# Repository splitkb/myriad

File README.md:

# Myriad

This repository stores the public documentation for the [Myriad System](https://myriad.splitkb.com/). Did you see any mistakes? Feel free to submit a pull request!

## Symbols & footprints
You can find KiCad symbols and footprints [here](assets/kicad/).

## Example projects
You can find some example projects [here](assets/example_projects/).

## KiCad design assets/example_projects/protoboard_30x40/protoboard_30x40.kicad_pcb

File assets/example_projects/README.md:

# Myriad Example projects
Having trouble getting started with your Myriad project? Why not [take a look](https://github.com/splitkb/myriad/archive/refs/heads/main.zip) at these example projects to get an idea of what the end result should look like.

_(Having trouble finding this directory in the ZIP? It's under `assets/kicad`!)_

## protoboard_??x??

Simple prototyping board. Exposes basic GPIO functionality on the bottom two rows, while providing 3-long strips on the rest of the card. You can use this to build your own simple modules, without having to get a PCB manufactured.

## breakout_22x30

Breakout board. Exposes all currently-available Myriad pins, making it ideal if you want to try connecting external hardware to it.

## Licensing

These files are available for **non-commercial use only**. See [https://myriad.splitkb.com/specification/terms_of_use.html](https://myriad.splitkb.com/specification/terms_of_use.html) for more information.

## More information

Are you looking for the specification, or just want to know more about the Myriad system in general? Visit [https://myriad.splitkb.com/](https://myriad.splitkb.com/)!

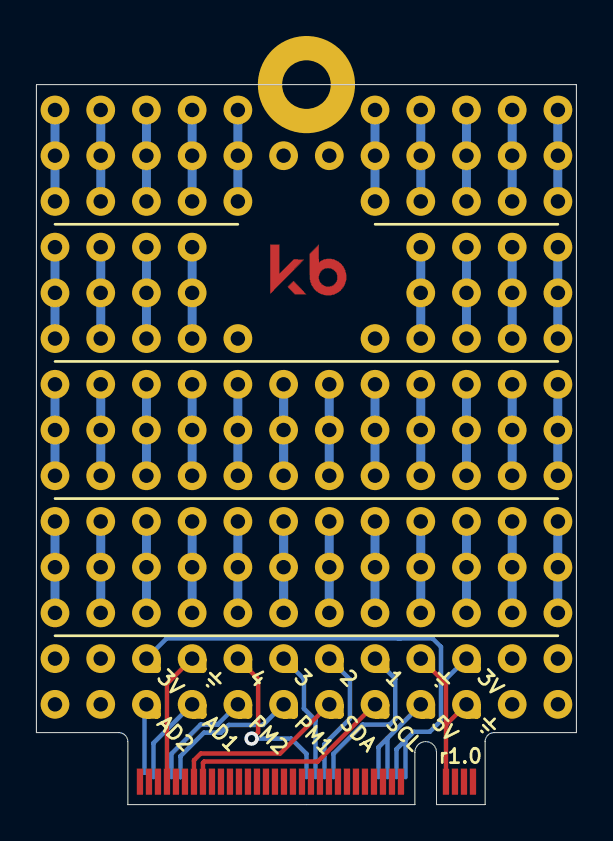
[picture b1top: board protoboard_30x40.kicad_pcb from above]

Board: 2 copper layers, 30.0 x 40.0 mm, 17 parts (0 on the bottom side), 11 nets.

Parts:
J1: Myriad_Module_Connector; Myriad_Module_30x40mm
J2: AD1; ProtoPad
J3: AD2; ProtoPad
J4: PM1; ProtoPad
J5: PM2; ProtoPad
J6: 1; ProtoPad
J7: 2; ProtoPad
J8: 3; ProtoPad
J9: 4; ProtoPad
J10: SDA; ProtoPad
J11: SCL; ProtoPad
J12: 5V; ProtoPad
J13, J16: 3V; ProtoPad
J14, J15, J17: GND; ProtoPad

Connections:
+3V3: J1.16 (PWR_3V), J1.18 (PWR_3V), J13.1, J16.1
+5V: J1.20 (PWR_5V), J1.22 (PWR_5V), J12.1
GND: J1.1 (GND), J1.7 (GND), J1.40 (GND), J1.46 (GND), J1.54 (GND), J1.57 (GND), J1.64 (GND), J1.69 (GND), J1.70 (GND), J14.1, J15.1, J17.1
unnamed: J1.17 (PWR_RAW), J1.19 (PWR_RAW), J1.21 (PWR_RAW), J1.23 (PWR_RAW)
unnamed: J1.32 (GPIO_1), J6.1
unnamed: J1.34 (GPIO_2), J7.1
unnamed: J1.36 (GPIO_3), J8.1
unnamed: J1.38 (GPIO_4), J9.1
unnamed: J1.61 (I2C_SCL), J11.1
unnamed: J1.63 (I2C_SDA), J10.1
unnamed: J1.68 (PWM_2), J5.1

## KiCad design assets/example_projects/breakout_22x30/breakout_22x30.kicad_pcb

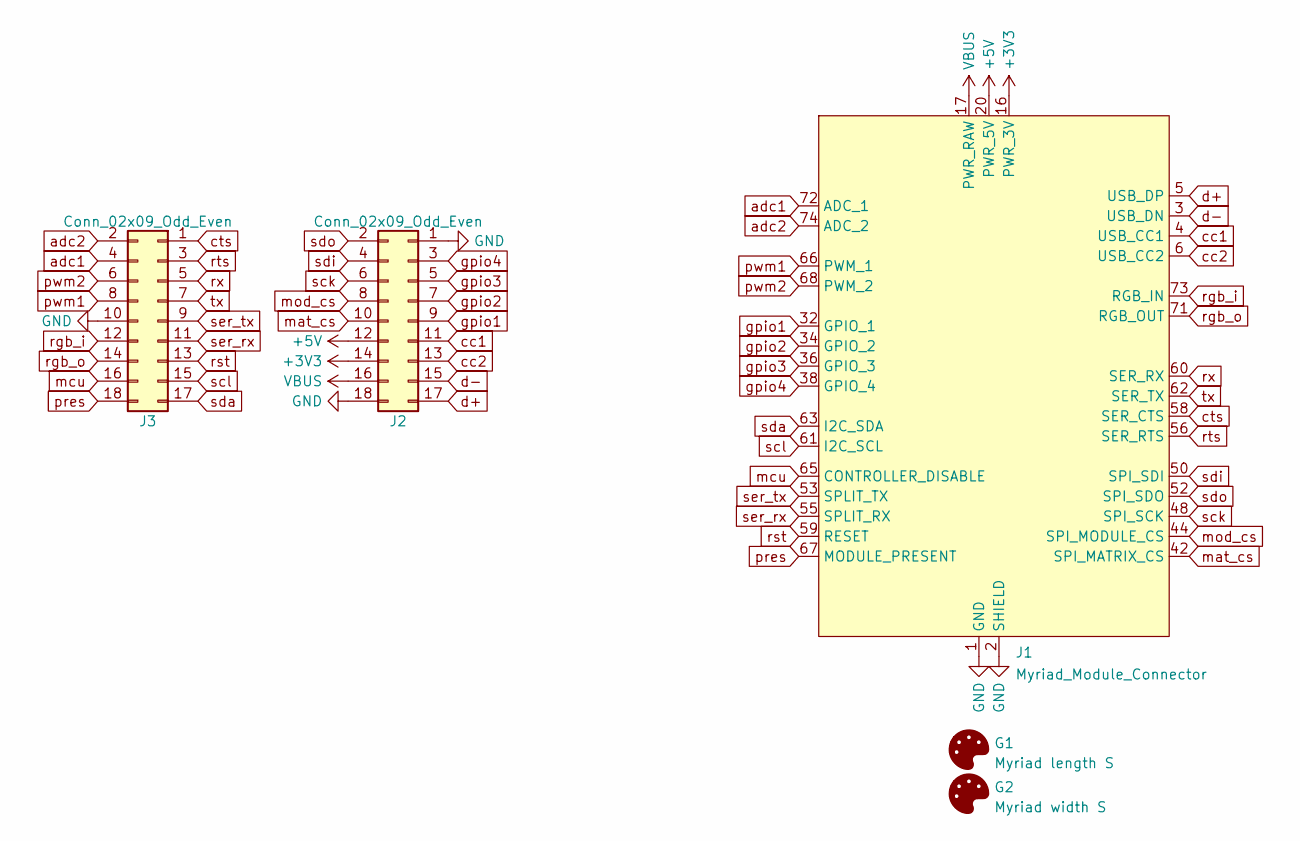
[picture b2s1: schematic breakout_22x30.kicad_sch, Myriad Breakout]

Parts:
G1: Myriad length S; Myriad_length-s
G2: Myriad width S; Myriad_width-s
J1: Myriad_Module_Connector; Myriad_Module_22x30mm
J2, J3: Conn_02x09_Odd_Even; PinSocket_2x09_P2.54mm_Vertical

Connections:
+3V3: J1.16 (PWR_3V), J1.18 (PWR_3V), J2.14
+5V: J1.20 (PWR_5V), J1.22 (PWR_5V), J2.12
GND: J1.1 (GND), J1.2 (SHIELD), J1.7 (GND), J1.40 (GND), J1.46 (GND), J1.54 (GND), J1.57 (GND), J1.64 (GND), J1.69 (GND), J1.70 (GND), J2.1, J2.18, J3.10
VBUS: J1.17 (PWR_RAW), J1.19 (PWR_RAW), J1.21 (PWR_RAW), J1.23 (PWR_RAW), J2.16
adc1: J1.72 (ADC_1), J3.4
adc2: J1.74 (ADC_2), J3.2
cc1: J1.4 (USB_CC1), J2.11
cc2: J1.6 (USB_CC2), J2.13
cts: J1.58 (SER_CTS), J3.1
d+: J1.5 (USB_DP), J2.17
d-: J1.3 (USB_DN), J2.15
gpio1: J1.32 (GPIO_1), J2.9
gpio2: J1.34 (GPIO_2), J2.7
gpio3: J1.36 (GPIO_3), J2.5
gpio4: J1.38 (GPIO_4), J2.3
mat_cs: J1.42 (SPI_MATRIX_CS), J2.10
mcu: J1.65 (CONTROLLER_DISABLE), J3.16
mod_cs: J1.44 (SPI_MODULE_CS), J2.8
pres: J1.67 (MODULE_PRESENT), J3.18
pwm1: J1.66 (PWM_1), J3.8
pwm2: J1.68 (PWM_2), J3.6
rgb_i: J1.73 (RGB_IN), J3.12
rgb_o: J1.71 (RGB_OUT), J3.14
rst: J1.59 (RESET), J3.13
rts: J1.56 (SER_RTS), J3.3
rx: J1.60 (SER_RX), J3.5
sck: J1.48 (SPI_SCK), J2.6
scl: J1.61 (I2C_SCL), J3.15
sda: J1.63 (I2C_SDA), J3.17
sdi: J1.50 (SPI_SDI), J2.4
sdo: J1.52 (SPI_SDO), J2.2
ser_rx: J1.55 (SPLIT_RX), J3.11
ser_tx: J1.53 (SPLIT_TX), J3.9
tx: J1.62 (SER_TX), J3.7

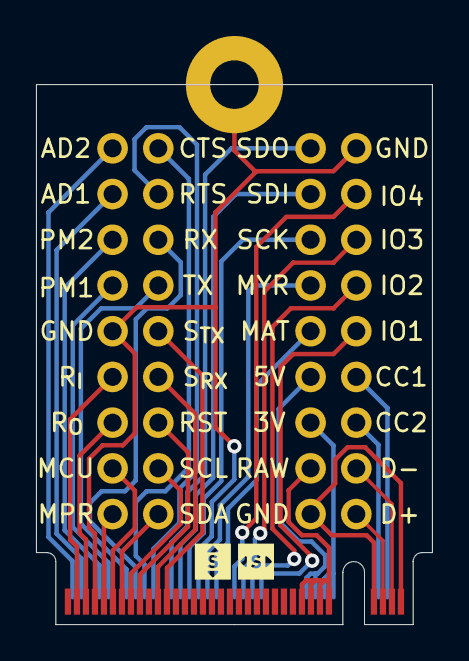
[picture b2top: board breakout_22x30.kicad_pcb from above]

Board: 2 copper layers, 22.0 x 30.0 mm, 5 parts (0 on the bottom side), 34 nets.

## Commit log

2023-10-03 Fix URL
2023-10-11 Update docs
2023-10-11 Fix links
2023-10-12 Fix vid / pid length
2023-10-16 Document endianness
2023-10-25 Bump just-the-docs from 0.6.2 to 0.7.0
    Bumps [just-the-docs](https://github.com/just-the-docs/just-the-docs) from 0.6.2 to 0.7.0.
    - [Release notes](https://github.com/just-the-docs/just-the-docs/releases)
    - [Changelog](https://github.com/just-the-docs/just-the-docs/blob/main/CHANGELOG.md)
    - [Commits](https://github.com/just-the-docs/just-the-docs/compare/v0.6.2...v0.7.0)
    ---
    updated-dependencies:
2023-12-27 Bump jekyll from 4.3.2 to 4.3.3
    Bumps [jekyll](https://github.com/jekyll/jekyll) from 4.3.2 to 4.3.3.
    - [Release notes](https://github.com/jekyll/jekyll/releases)
    - [Changelog](https://github.com/jekyll/jekyll/blob/v4.3.3/History.markdown)
    - [Commits](https://github.com/jekyll/jekyll/compare/v4.3.2...v4.3.3)
    ---
    updated-dependencies:
2024-02-23 Bump just-the-docs from 0.6.2 to 0.8.0
    Bumps [just-the-docs](https://github.com/just-the-docs/just-the-docs) from 0.6.2 to 0.8.0.
    - [Release notes](https://github.com/just-the-docs/just-the-docs/releases)
    - [Changelog](https://github.com/just-the-docs/just-the-docs/blob/main/CHANGELOG.md)
    - [Commits](https://github.com/just-the-docs/just-the-docs/compare/v0.6.2...v0.8.0)
    ---
    updated-dependencies:
2024-03-07 Bump just-the-docs from 0.6.2 to 0.8.1
    Bumps [just-the-docs](https://github.com/just-the-docs/just-the-docs) from 0.6.2 to 0.8.1.
    - [Release notes](https://github.com/just-the-docs/just-the-docs/releases)
    - [Changelog](https://github.com/just-the-docs/just-the-docs/blob/main/CHANGELOG.md)
    - [Commits](https://github.com/just-the-docs/just-the-docs/compare/v0.6.2...v0.8.1)
    ---
    updated-dependencies:
